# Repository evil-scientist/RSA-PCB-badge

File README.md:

# RSA-PCB-Badge
A Robotic Student Association PCB Badge which was designed and soldered at a workshop

<!-- PROJECT LOGO -->
<br />
<p align="center">
  
  <h1 align="center">RSA-Badge v1.0</h1>

</p>
   
## About The Project
This printed board circuit (pcb), the RSA badge, is meant to be used to learn about PCB design and hardware. It was designed and developed as part of the PCB design workshop as a beginner friendly introduction to the world of hardware.

## Learn more
You can follow the slides from the workshop (part one) [here](https://docs.google.com/presentation/d/1rfjJbtmV363k_88A-ob4LZY-vbHJMEZujSK3JvL_T38/edit?usp=sharing) 

## Features
A board with a blinky LED powered by a CR2032 3V cell that you can pin anywhere! 

## Contributing
Any contributions you make are greatly appreciated.
- Create new examples and submit them in a github issue and upload files.
- You can also submit examples via merge request if you are comfortable with using git.
- Replicate the badge and give feedback. 

## Contact
RSA website: [rsadelft.nl](https://rsadelft.nl/))

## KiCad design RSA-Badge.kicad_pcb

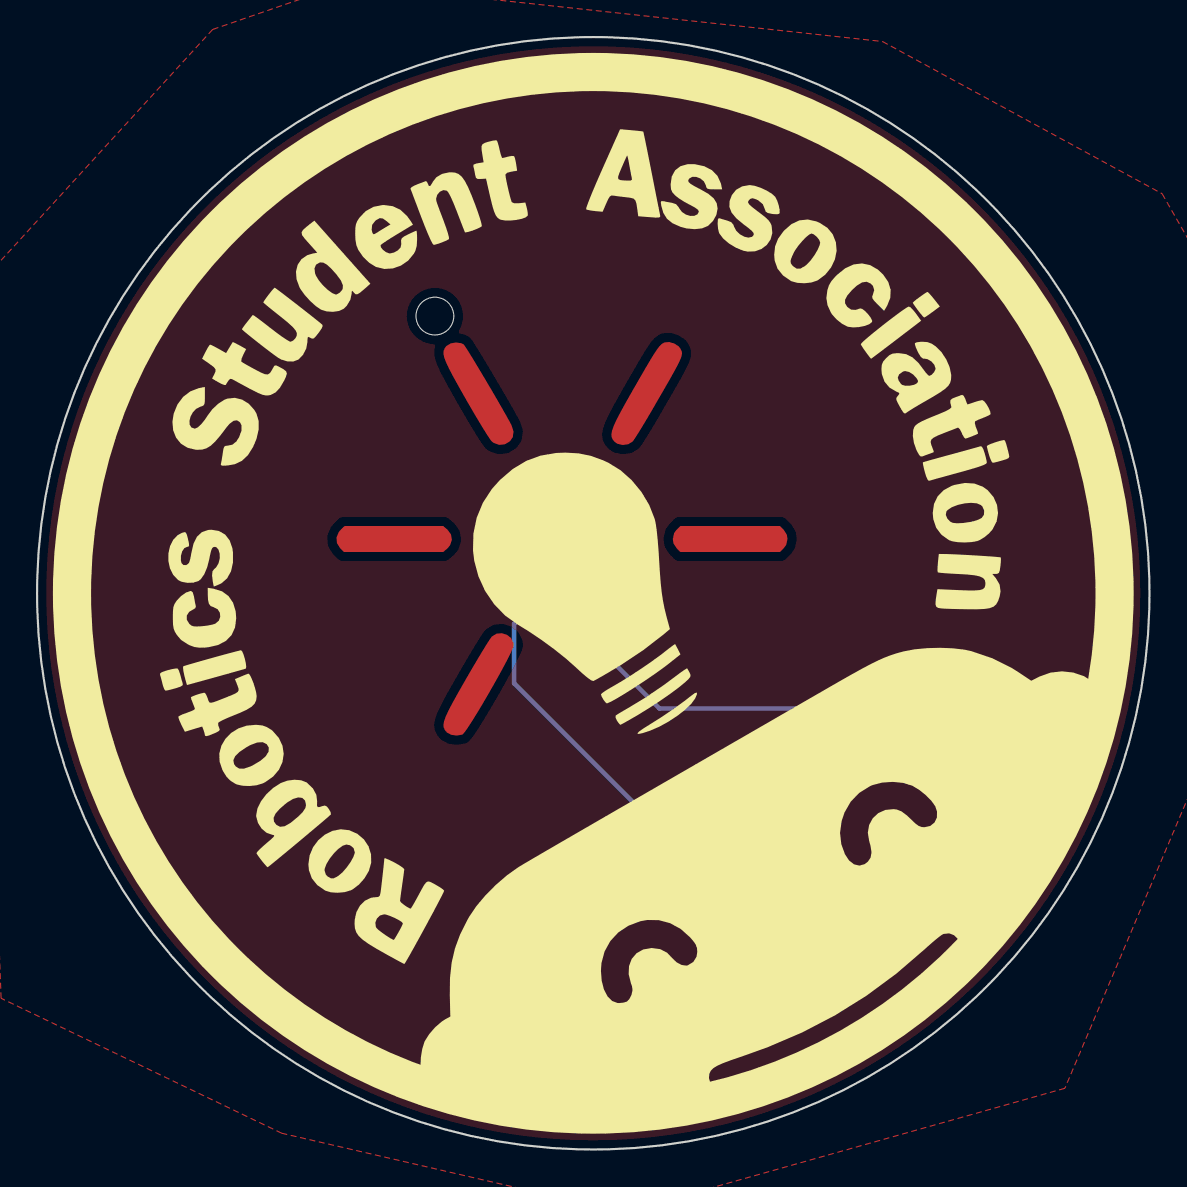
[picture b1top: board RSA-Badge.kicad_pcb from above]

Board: 2 copper layers, 61.8 x 61.8 mm, 4 parts (1 on the bottom side), 3 nets.

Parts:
BT1: 3V CR2032; BatteryHolder_Keystone_106_1x20mm
D1: Red; LED_D3.0mm_Horizontal_O1.27mm_Z2.0mm
R1: 100R; R_Axial_DIN0207_L6.3mm_D2.5mm_P10.16mm_Horizontal
U1: BADGE_PIN; MountingHole_2.1mm

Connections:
/LED_N: D1.1 (K), R1.2
GND: BT1.2 (-), R1.1
VCC: BT1.1 (+), D1.2 (A)

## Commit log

2022-05-18 Add all PCB files
